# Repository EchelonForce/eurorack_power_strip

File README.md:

# Eurorack Power Strip

This is a PCB for power distribution for eurorack.

Full writeup here: https://www.robotdialogs.com/2022/09/eurorack-power-distribution-pcb.html

This work is licensed under a Creative Commons Attribution-NonCommercial-ShareAlike 4.0 International License. https://creativecommons.org/licenses/by-nc-sa/4.0/

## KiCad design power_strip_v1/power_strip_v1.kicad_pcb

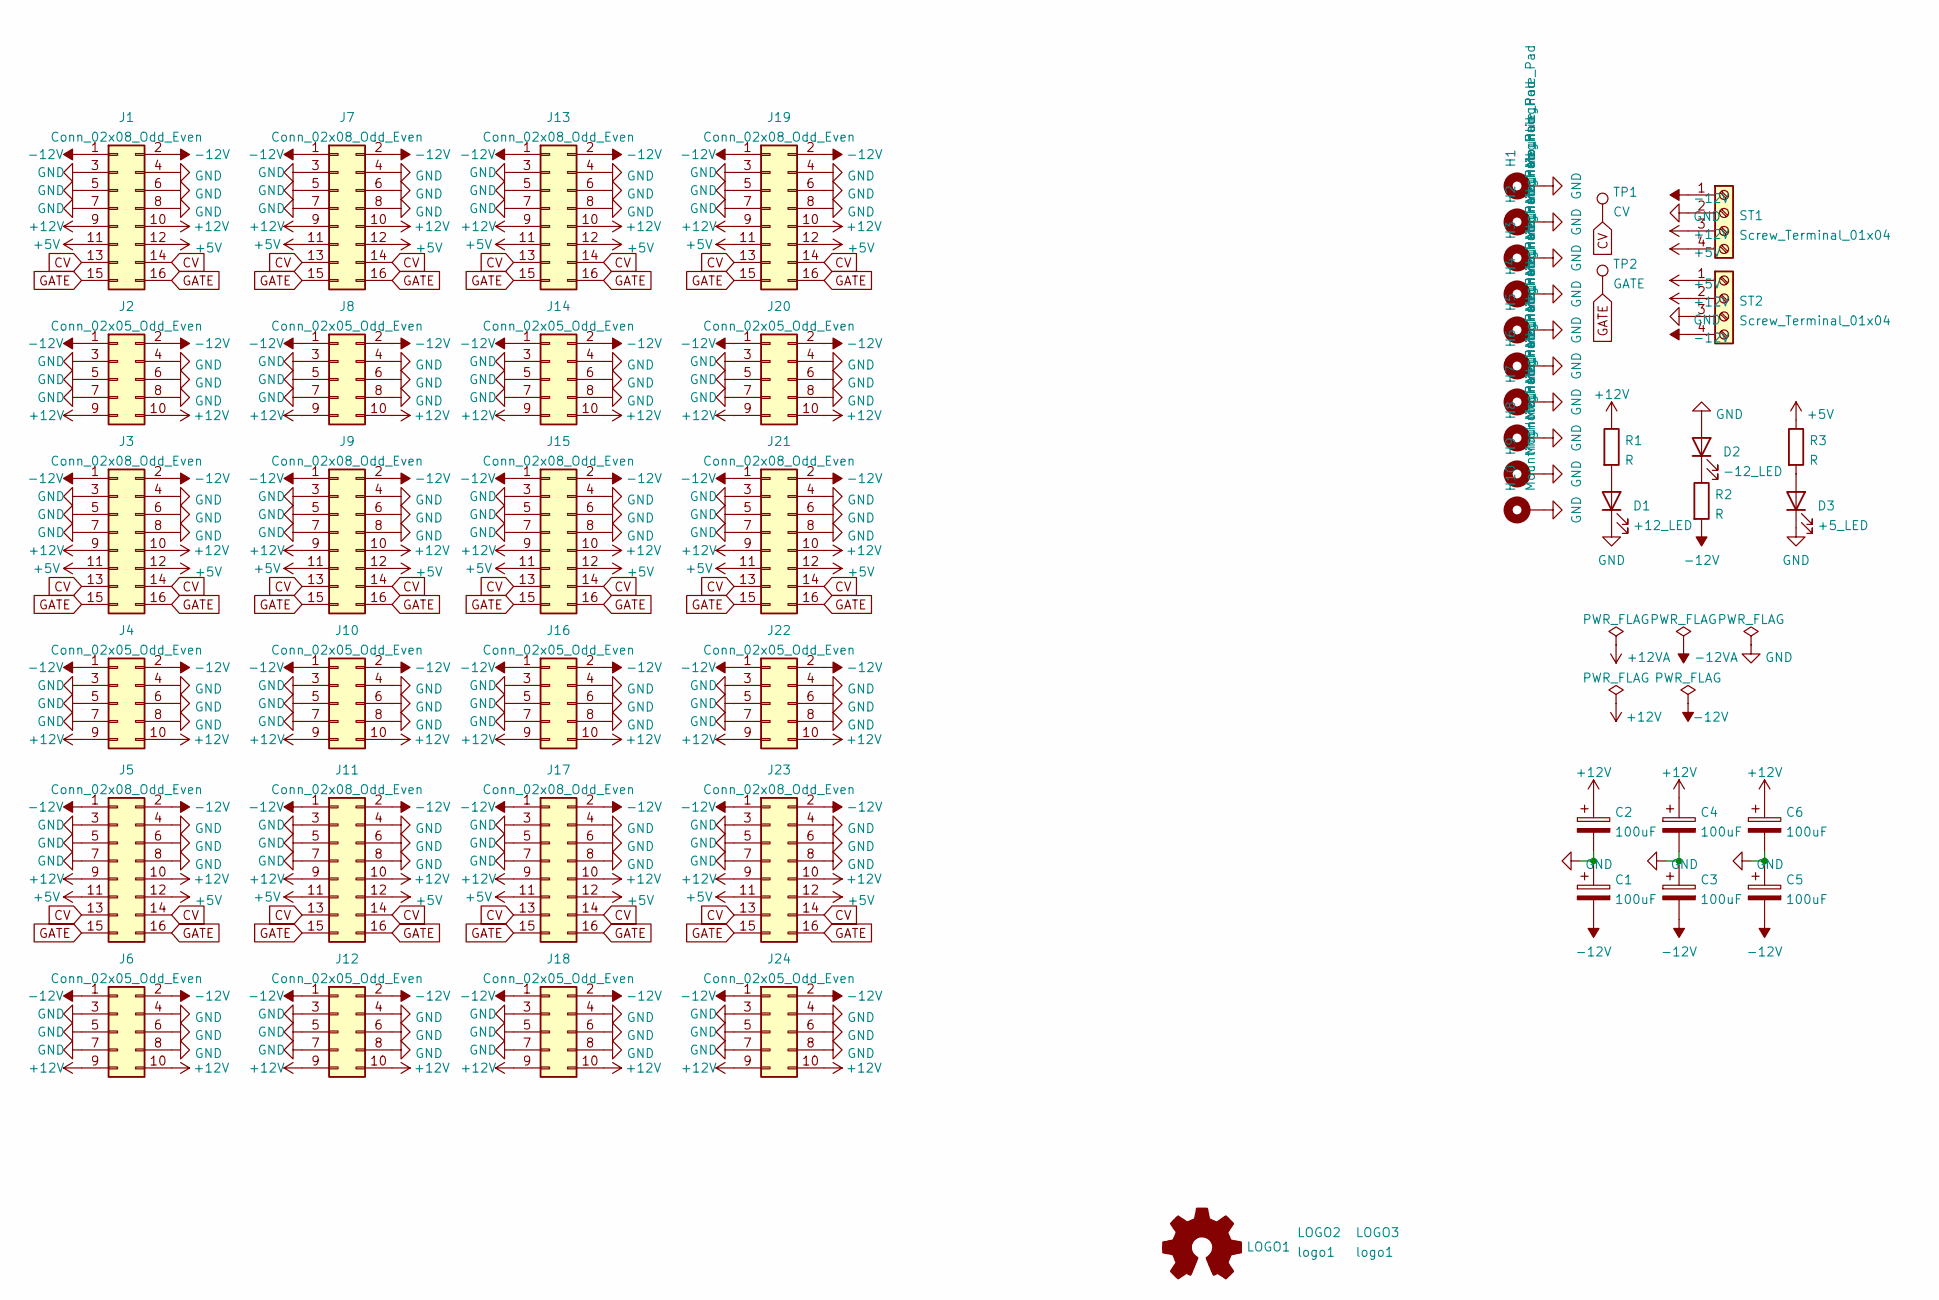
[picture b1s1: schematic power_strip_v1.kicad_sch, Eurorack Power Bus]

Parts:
C1, C2, C3, C4, C5, C6: 100uF; CP_Radial_D5.0mm_P2.50mm
D1: +12_LED; LED_D3.0mm
D2: -12_LED; LED_D3.0mm
D3: +5_LED; LED_D3.0mm
H1, H2, H3, H4, H5, H6, H7, H8, H9, H10: MountingHole_Pad; MountingHole_3.5mm_Pad_TopBottom
J1, J3, J5, J7, J9, J11, J13, J15, J17, J19, J21, J23: Conn_02x08_Odd_Even; IDC-Header_2x08_P2.54mm_Vertical
J2, J4, J6, J8, J10, J12, J14, J16, J18, J20, J22, J24: Conn_02x05_Odd_Even; IDC-Header_2x05_P2.54mm_Vertical
LOGO1: Logo_Open_Hardware_Small; OSHW-Symbol_6.7x6mm_SilkScreen
LOGO2: logo1; Logo1
LOGO3: logo1; Logo2
R1, R2, R3: R; R_Axial_DIN0204_L3.6mm_D1.6mm_P7.62mm_Horizontal
ST1, ST2: Screw_Terminal_01x04; TerminalBlock_Phoenix_MKDS-1,5-4_1x04_P5.00mm_Horizontal
TP1: CV; TestPoint_THTPad_D2.5mm_Drill1.2mm
TP2: GATE; TestPoint_THTPad_D2.5mm_Drill1.2mm

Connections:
+5V: J1.11, J1.12, J3.11, J3.12, J5.11, J5.12, J7.11, J7.12, J9.11, J9.12, J11.11, J11.12, J13.11, J13.12, J15.11, J15.12, J17.11, J17.12, J19.11, J19.12, J21.11, J21.12, J23.11, J23.12, R3.1, ST1.4, ST2.1
+12V: C2.1, C4.1, C6.1, J1.9, J1.10, J2.9, J2.10, J3.9, J3.10, J4.9, J4.10, J5.9, J5.10, J6.9, J6.10, J7.9, J7.10, J8.9, J8.10, J9.9, J9.10, J10.9, J10.10, J11.9, J11.10, J12.9, J12.10, J13.9, J13.10, J14.9, J14.10, J15.9, J15.10, J16.9, J16.10, J17.9, J17.10, J18.9, J18.10, J19.9, J19.10, J20.9, J20.10, J21.9, J21.10, J22.9, J22.10, J23.9, J23.10, J24.9, J24.10, R1.1, ST1.3, ST2.2
-12V: C1.2, C3.2, C5.2, J1.1, J1.2, J2.1, J2.2, J3.1, J3.2, J4.1, J4.2, J5.1, J5.2, J6.1, J6.2, J7.1, J7.2, J8.1, J8.2, J9.1, J9.2, J10.1, J10.2, J11.1, J11.2, J12.1, J12.2, J13.1, J13.2, J14.1, J14.2, J15.1, J15.2, J16.1, J16.2, J17.1, J17.2, J18.1, J18.2, J19.1, J19.2, J20.1, J20.2, J21.1, J21.2, J22.1, J22.2, J23.1, J23.2, J24.1, J24.2, R2.2, ST1.1, ST2.4
CV: J1.13, J1.14, J3.13, J3.14, J5.13, J5.14, J7.13, J7.14, J9.13, J9.14, J11.13, J11.14, J13.13, J13.14, J15.13, J15.14, J17.13, J17.14, J19.13, J19.14, J21.13, J21.14, J23.13, J23.14, TP1.1
GATE: J1.15, J1.16, J3.15, J3.16, J5.15, J5.16, J7.15, J7.16, J9.15, J9.16, J11.15, J11.16, J13.15, J13.16, J15.15, J15.16, J17.15, J17.16, J19.15, J19.16, J21.15, J21.16, J23.15, J23.16, TP2.1
GND: C1.1, C2.2, C3.1, C4.2, C5.1, C6.2, D1.1 (K), D2.2 (A), D3.1 (K), H1.1, H2.1, H3.1, H4.1, H5.1, H6.1, H7.1, H8.1, H9.1, H10.1, J1.3, J1.4, J1.5, J1.6, J1.7, J1.8, J2.3, J2.4, J2.5, J2.6, J2.7, J2.8, J3.3, J3.4, J3.5, J3.6, J3.7, J3.8, J4.3, J4.4, J4.5, J4.6, J4.7, J4.8, J5.3, J5.4, J5.5, J5.6, J5.7, J5.8, J6.3, J6.4, J6.5, J6.6, J6.7, J6.8, J7.3, J7.4, J7.5, J7.6, J7.7, J7.8, J8.3, J8.4, J8.5, J8.6, J8.7, J8.8, J9.3, J9.4, J9.5, J9.6, J9.7, J9.8, J10.3, J10.4, J10.5, J10.6, J10.7, J10.8, J11.3, J11.4, J11.5, J11.6, J11.7, J11.8, J12.3, J12.4, J12.5, J12.6, J12.7, J12.8, J13.3, J13.4, J13.5, J13.6, J13.7, J13.8, J14.3, J14.4, J14.5, J14.6, J14.7, J14.8, J15.3, J15.4, J15.5, J15.6, J15.7, J15.8, J16.3, J16.4, J16.5, J16.6, J16.7, J16.8, J17.3, J17.4, J17.5, J17.6, J17.7, J17.8, J18.3, J18.4, J18.5, J18.6, J18.7, J18.8, J19.3, J19.4, J19.5, J19.6, J19.7, J19.8, J20.3, J20.4, J20.5, J20.6, J20.7, J20.8, J21.3, J21.4, J21.5, J21.6, J21.7, J21.8, J22.3, J22.4, J22.5, J22.6, J22.7, J22.8, J23.3, J23.4, J23.5, J23.6, J23.7, J23.8, J24.3, J24.4, J24.5, J24.6, J24.7, J24.8, ST1.2, ST2.3
unnamed: D1.2 (A), R1.2
unnamed: D2.1 (K), R2.1
unnamed: D3.2 (A), R3.2

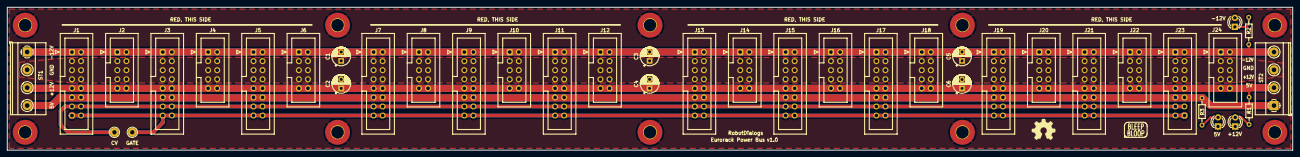
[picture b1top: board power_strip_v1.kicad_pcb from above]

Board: 2 copper layers, 360.0 x 40.0 mm, 53 parts (0 on the bottom side), 9 nets.

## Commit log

2022-02-08 Initial Commit, .gitignore
2022-02-19 Version 1 PCB as ordered
2022-09-02 Notes and schematic v1 pdf
2022-09-02 Add readme
